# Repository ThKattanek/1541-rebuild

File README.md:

# 1541-rebuild
Ersetzt den Analogteil einer Floppy 1541 durch ein Micro Controller der Disk Images per SD Karte lesen kann. Mit dieser Hardware ist es möglich ein Board wo der Analogteil defekt ist, durch diese wieder zum laufen zu bringen. Das schreiben ist nun auch schon enthalten. Es wird lediglich die 1541 Platine, diese Hardware und ein 5VDC Netzteil benötigt, oder auch das Originale Netzteil. An der 1541 II Platine muss eine Änderungen vorgenommen werden und zwar die (VIA2 (DC) sockeln.

#### ** Danke [F00K42](https://github.com/fook42) für die Entwicklung der Schreibroutinen für D64 Images. **

### [Letzte Offizelle Version findet ihr hier](https://github.com/ThKattanek/1541-rebuild/releases/latest)

### Hardware / Schaltplan
Die Hardware wird mit KiCad entwickelt. Version 5.1.4 unter Ubuntu.

### Hier der Thread dazu im Forum64
https://www.forum64.de/index.php?thread/59884-laufwerk-der-1541-emulieren

### Einige Videos von der 1541-rebuild in aktion
https://youtu.be/EGB8lYKcW-g

https://www.youtube.com/watch?v=MlbUPTzcQGI&t=36s

https://www.youtube.com/watch?v=gKM73VpHdTw&t=256s

### Verwendete Libs
LCD Ansteuerung von Mikrokontroller.net: http://www.mikrocontroller.net/articles/AVR-GCC-Tutorial/LCD-Ansteuerung

SD/FAT System von Roland Riegel: http://www.roland-riegel.de/sd-reader/

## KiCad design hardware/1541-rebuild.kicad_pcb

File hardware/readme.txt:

Die Hardware wurde mit KiCad Version 5.1.4 erstellt.

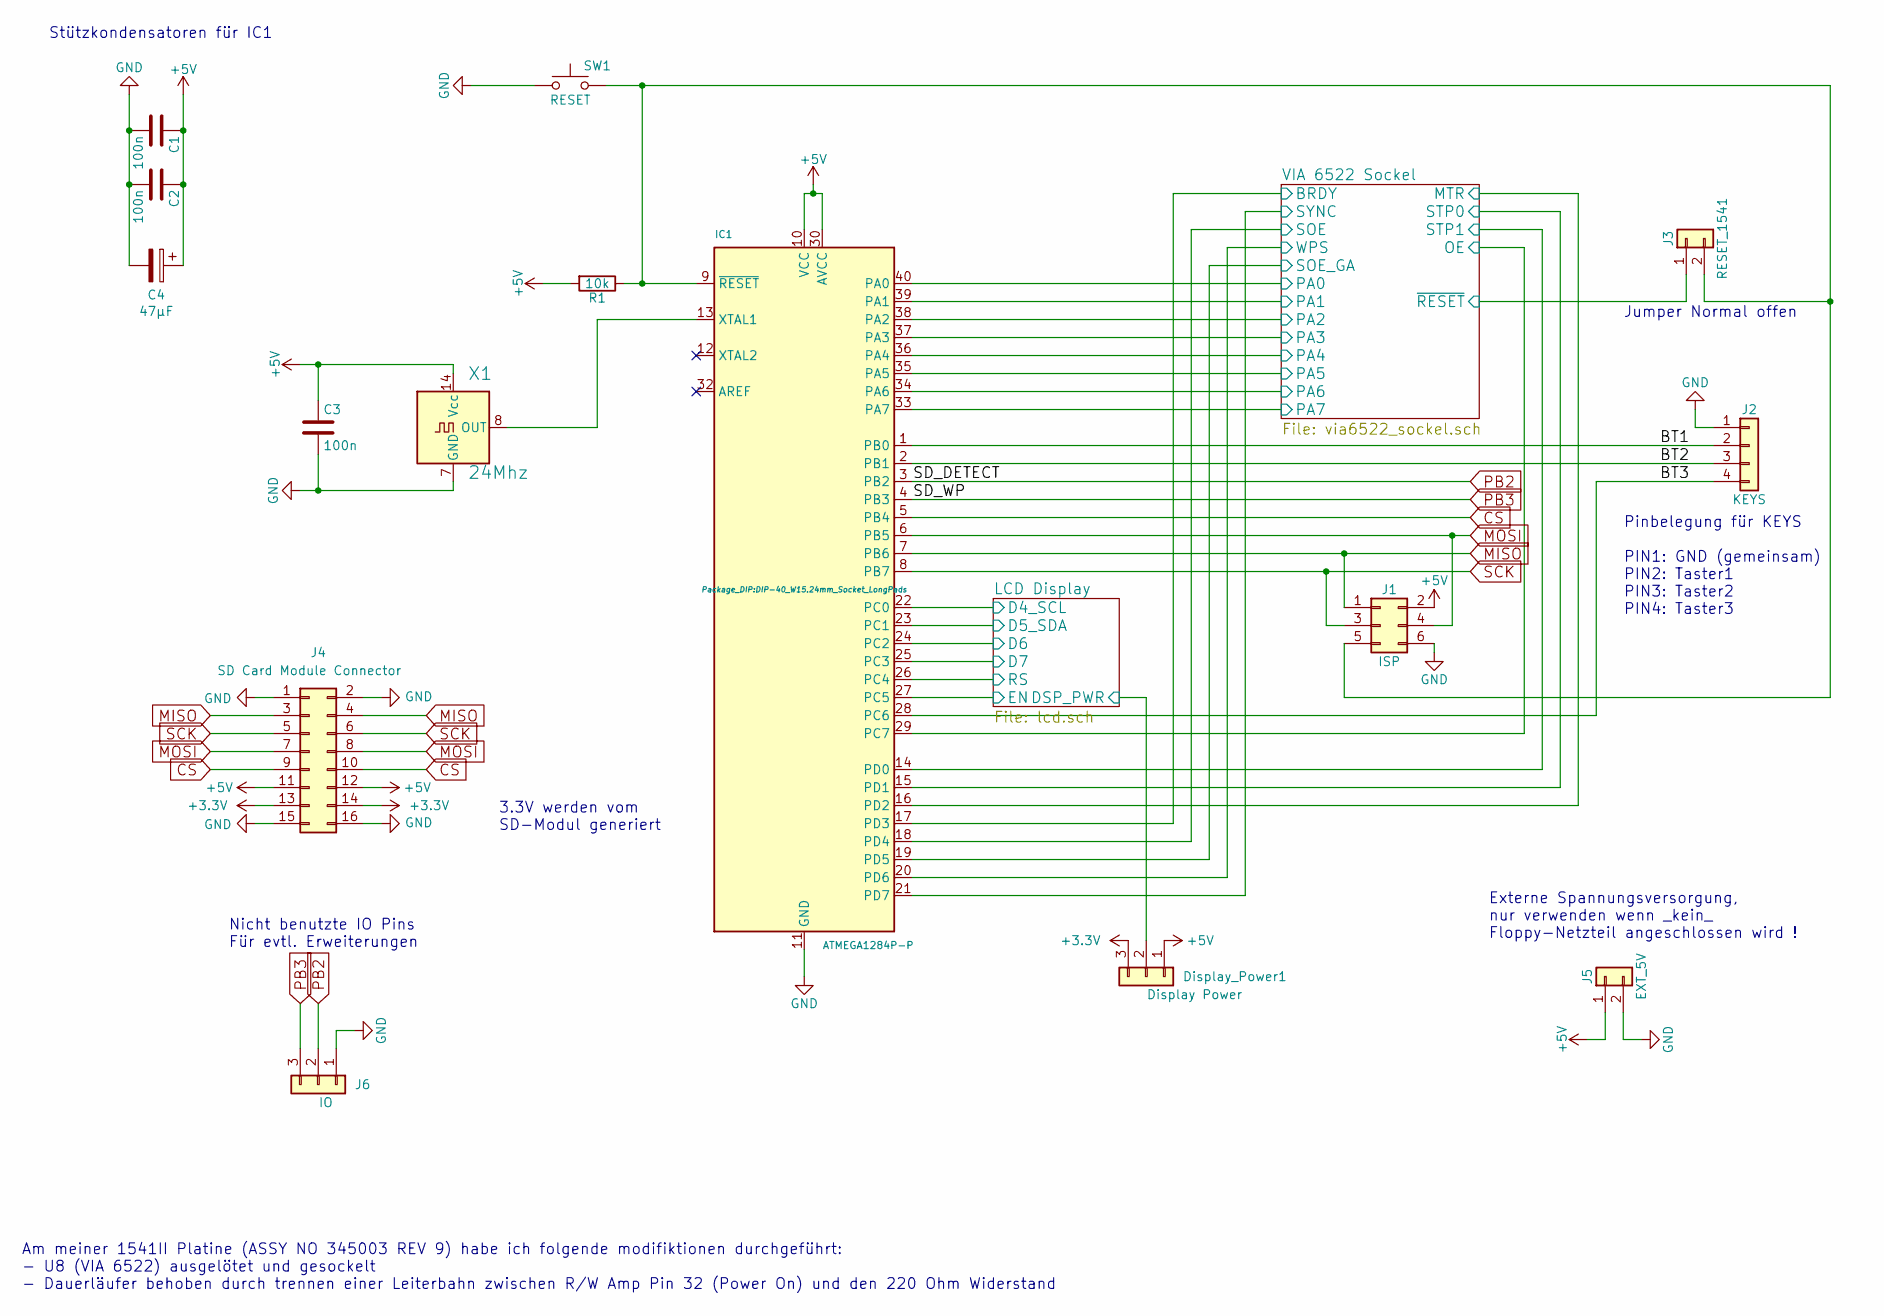
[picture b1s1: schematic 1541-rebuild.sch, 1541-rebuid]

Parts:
C1, C2, C3: 100n; C_Disc_D3.4mm_W2.1mm_P2.50mm
C4: 47µF; CP_Radial_D5.0mm_P2.50mm
Display_Power1: Display Power; PinHeader_1x03_P2.54mm_Vertical
IC1: ATMEGA1284P-P; DIP-40_W15.24mm_Socket_LongPads
J1: ISP; IDC-Header_2x03_P2.54mm_Vertical
J2: KEYS; PinHeader_1x04_P2.54mm_Vertical
J3: RESET_1541; PinHeader_1x02_P2.54mm_Vertical
J4: SD Card Module Connector; PinSocket_2x08_P2.54mm_Vertical
J5: EXT_5V; PinHeader_1x02_P2.54mm_Vertical
J6: IO; PinHeader_1x03_P2.54mm_Vertical
R1: 10k; R_Axial_DIN0207_L6.3mm_D2.5mm_P10.16mm_Horizontal
SW1: RESET; SW_PUSH_6mm_H5mm
X1: 24Mhz; Oscillator_DIP-14_LargePads

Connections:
+3V3: Display_Power1.3, J4.13, J4.14
+5V: C1.1, C2.1, C3.1, C4.1, Display_Power1.1, IC1.10 (VCC), IC1.30 (AVCC), J1.2, J4.11, J4.12, J5.1, R1.2, X1.14 (Vcc); also elsewhere on the board
/BT1: IC1.1 (PB0), J2.2
/BT2: IC1.2 (PB1), J2.3
/BT3: IC1.28 (PC6), J2.4
/LCD Display/D4_SCL: IC1.22 (PC0); also elsewhere on the board
/LCD Display/D5_SDA: IC1.23 (PC1); also elsewhere on the board
/LCD Display/D6: IC1.24 (PC2); also elsewhere on the board
/LCD Display/D7: IC1.25 (PC3); also elsewhere on the board
/LCD Display/DSP_PWR: Display_Power1.2; also elsewhere on the board
/LCD Display/EN: IC1.27 (PC5); also elsewhere on the board
/LCD Display/RS: IC1.26 (PC4); also elsewhere on the board
/VIA 6522 Sockel/BRDY: IC1.17 (PD3); also elsewhere on the board
/VIA 6522 Sockel/MTR: IC1.16 (PD2); also elsewhere on the board
/VIA 6522 Sockel/OE: IC1.29 (PC7); also elsewhere on the board
/VIA 6522 Sockel/PA0: IC1.40 (PA0); also elsewhere on the board
/VIA 6522 Sockel/PA1: IC1.39 (PA1); also elsewhere on the board
/VIA 6522 Sockel/PA2: IC1.38 (PA2); also elsewhere on the board
/VIA 6522 Sockel/PA3: IC1.37 (PA3); also elsewhere on the board
/VIA 6522 Sockel/PA4: IC1.36 (PA4); also elsewhere on the board
/VIA 6522 Sockel/PA5: IC1.35 (PA5); also elsewhere on the board
/VIA 6522 Sockel/PA6: IC1.34 (PA6); also elsewhere on the board
/VIA 6522 Sockel/PA7: IC1.33 (PA7); also elsewhere on the board
/VIA 6522 Sockel/SOE: IC1.18 (PD4); also elsewhere on the board
/VIA 6522 Sockel/SOE_GA: IC1.19 (PD5); also elsewhere on the board
/VIA 6522 Sockel/STP0: IC1.15 (PD1); also elsewhere on the board
/VIA 6522 Sockel/STP1: IC1.14 (PD0); also elsewhere on the board
/VIA 6522 Sockel/SYNC: IC1.21 (PD7); also elsewhere on the board
/VIA 6522 Sockel/WPS: IC1.20 (PD6); also elsewhere on the board
/VIA 6522 Sockel/~RESET: J3.1; also elsewhere on the board
CS: IC1.5 (PB4), J4.9, J4.10
GND: C1.2, C2.2, C3.2, C4.2, IC1.11 (GND), IC1.31 (GND), J1.6, J2.1, J4.1, J4.2, J4.15, J4.16, J5.2, J6.1, SW1.1, X1.7 (GND); also elsewhere on the board
MISO: IC1.7 (PB6), J1.1, J4.3, J4.4
MOSI: IC1.6 (PB5), J1.4, J4.7, J4.8
unnamed: IC1.9 (~RESET), J1.5, J3.2, R1.1, SW1.2
unnamed: IC1.13 (XTAL1), X1.8 (OUT)
PB2: IC1.3 (PB2), J6.2
PB3: IC1.4 (PB3), J6.3
SCK: IC1.8 (PB7), J1.3, J4.5, J4.6

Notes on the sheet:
Am meiner 1541II Platine (ASSY NO 345003 REV 9) habe ich folgende modifiktionen durchgeführt: - U8 (VIA 6522) ausgelötet und gesockelt - Dauerläufer behoben durch trennen einer Leiterbahn zwischen R/W Amp Pin 32 (Power On) und den 220 Ohm Widerstand
Stützkondensatoren für IC1
Jumper Normal offen
Pinbelegung für KEYS PIN1: GND (gemeinsam) PIN2: Taster1 PIN3: Taster2 PIN4: Taster3
Externe Spannungsversorgung, nur verwenden wenn _kein_ Floppy-Netzteil angeschlossen wird !
Nicht benutzte IO Pins Für evtl. Erweiterungen
3.3V werden vom SD-Modul generiert

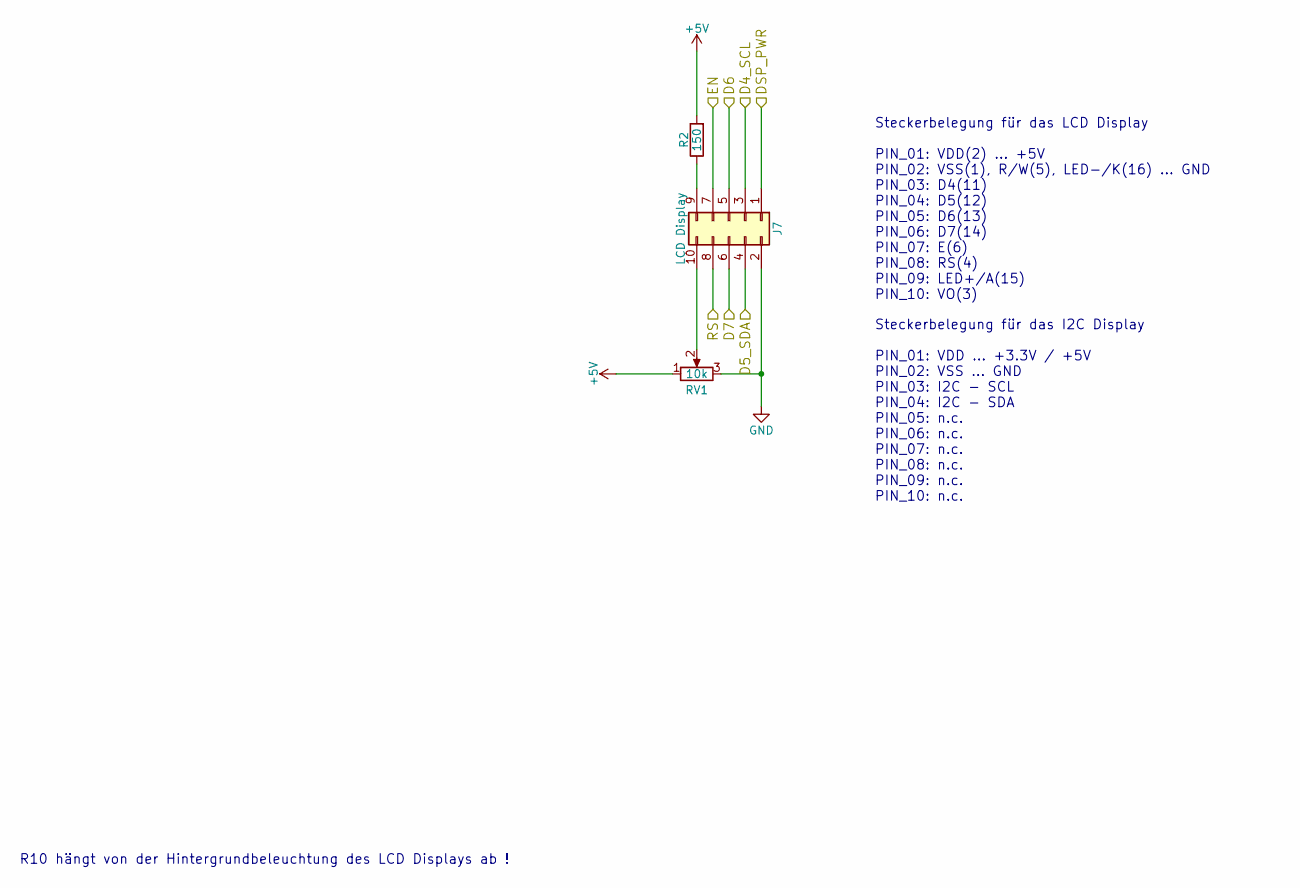
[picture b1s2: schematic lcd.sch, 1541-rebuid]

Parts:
J7: LCD Display; IDC-Header_2x05_P2.54mm_Vertical
R2: 150; R_Axial_DIN0207_L6.3mm_D2.5mm_P10.16mm_Horizontal
RV1: 10k; Potentiometer_Bourns_3296W_Vertical

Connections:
+5V: R2.2, RV1.1; also elsewhere on the board
/LCD Display/D4_SCL: J7.3; also elsewhere on the board
/LCD Display/D5_SDA: J7.4; also elsewhere on the board
/LCD Display/D6: J7.5; also elsewhere on the board
/LCD Display/D7: J7.6; also elsewhere on the board
/LCD Display/DSP_PWR: J7.1; also elsewhere on the board
/LCD Display/EN: J7.7; also elsewhere on the board
/LCD Display/RS: J7.8; also elsewhere on the board
GND: J7.2, RV1.3; also elsewhere on the board
unnamed: J7.9, R2.1
unnamed: J7.10, RV1.2

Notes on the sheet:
Steckerbelegung für das LCD Display PIN_01: VDD(2) ... +5V PIN_02: VSS(1), R/W(5), LED-/K(16) ... GND PIN_03: D4(11) PIN_04: D5(12) PIN_05: D6(13) PIN_06: D7(14) PIN_07: E(6) PIN_08: RS(4) PIN_09: LED+/A(15) PIN_10: VO(3)
R10 hängt von der Hintergrundbeleuchtung des LCD Displays ab !
Steckerbelegung für das I2C Display PIN_01: VDD ... +3.3V / +5V PIN_02: VSS ... GND PIN_03: I2C - SCL PIN_04: I2C - SDA PIN_05: n.c. PIN_06: n.c. PIN_07: n.c. PIN_08: n.c. PIN_09: n.c. PIN_10: n.c.

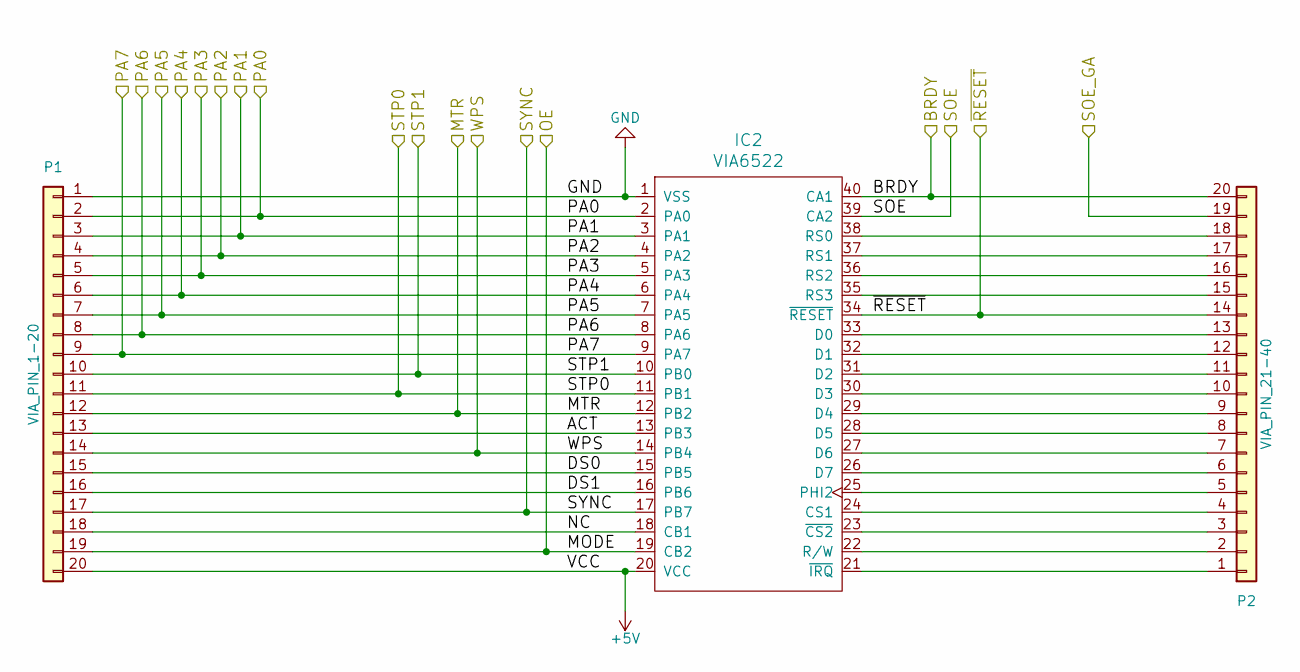
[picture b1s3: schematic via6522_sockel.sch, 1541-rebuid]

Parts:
IC2: VIA6522; DIP-40_W15.24mm_Socket_LongPads
P1: VIA_PIN_1-20; PinHeader_1x20_P2.54mm_Vertical
P2: VIA_PIN_21-40; PinHeader_1x20_P2.54mm_Vertical

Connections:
+5V: IC2.20 (VCC), P1.20; also elsewhere on the board
/VIA 6522 Sockel/ACT: IC2.13 (PB3), P1.13
/VIA 6522 Sockel/BRDY: IC2.40 (CA1), P2.20; also elsewhere on the board
/VIA 6522 Sockel/DS0: IC2.15 (PB5), P1.15
/VIA 6522 Sockel/DS1: IC2.16 (PB6), P1.16
/VIA 6522 Sockel/MTR: IC2.12 (PB2), P1.12; also elsewhere on the board
/VIA 6522 Sockel/NC: IC2.18 (CB1), P1.18
/VIA 6522 Sockel/OE: IC2.19 (CB2), P1.19; also elsewhere on the board
/VIA 6522 Sockel/PA0: IC2.2 (PA0), P1.2; also elsewhere on the board
/VIA 6522 Sockel/PA1: IC2.3 (PA1), P1.3; also elsewhere on the board
/VIA 6522 Sockel/PA2: IC2.4 (PA2), P1.4; also elsewhere on the board
/VIA 6522 Sockel/PA3: IC2.5 (PA3), P1.5; also elsewhere on the board
/VIA 6522 Sockel/PA4: IC2.6 (PA4), P1.6; also elsewhere on the board
/VIA 6522 Sockel/PA5: IC2.7 (PA5), P1.7; also elsewhere on the board
/VIA 6522 Sockel/PA6: IC2.8 (PA6), P1.8; also elsewhere on the board
/VIA 6522 Sockel/PA7: IC2.9 (PA7), P1.9; also elsewhere on the board
/VIA 6522 Sockel/SOE: IC2.39 (CA2); also elsewhere on the board
/VIA 6522 Sockel/SOE_GA: P2.19; also elsewhere on the board
/VIA 6522 Sockel/STP0: IC2.11 (PB1), P1.11; also elsewhere on the board
/VIA 6522 Sockel/STP1: IC2.10 (PB0), P1.10; also elsewhere on the board
/VIA 6522 Sockel/SYNC: IC2.17 (PB7), P1.17; also elsewhere on the board
/VIA 6522 Sockel/WPS: IC2.14 (PB4), P1.14; also elsewhere on the board
/VIA 6522 Sockel/~RESET: IC2.34 (~RESET), P2.14; also elsewhere on the board
GND: IC2.1 (VSS), P1.1; also elsewhere on the board
unnamed: IC2.21 (~IRQ), P2.1
unnamed: IC2.22 (R/W), P2.2
unnamed: IC2.23 (~CS2), P2.3
unnamed: IC2.24 (CS1), P2.4
unnamed: IC2.25 (PHI2), P2.5
unnamed: IC2.26 (D7), P2.6
unnamed: IC2.27 (D6), P2.7
unnamed: IC2.28 (D5), P2.8
unnamed: IC2.29 (D4), P2.9
unnamed: IC2.30 (D3), P2.10
unnamed: IC2.31 (D2), P2.11
unnamed: IC2.32 (D1), P2.12
unnamed: IC2.33 (D0), P2.13
unnamed: IC2.35 (RS3), P2.15
unnamed: IC2.36 (RS2), P2.16
unnamed: IC2.37 (RS1), P2.17
unnamed: IC2.38 (RS0), P2.18

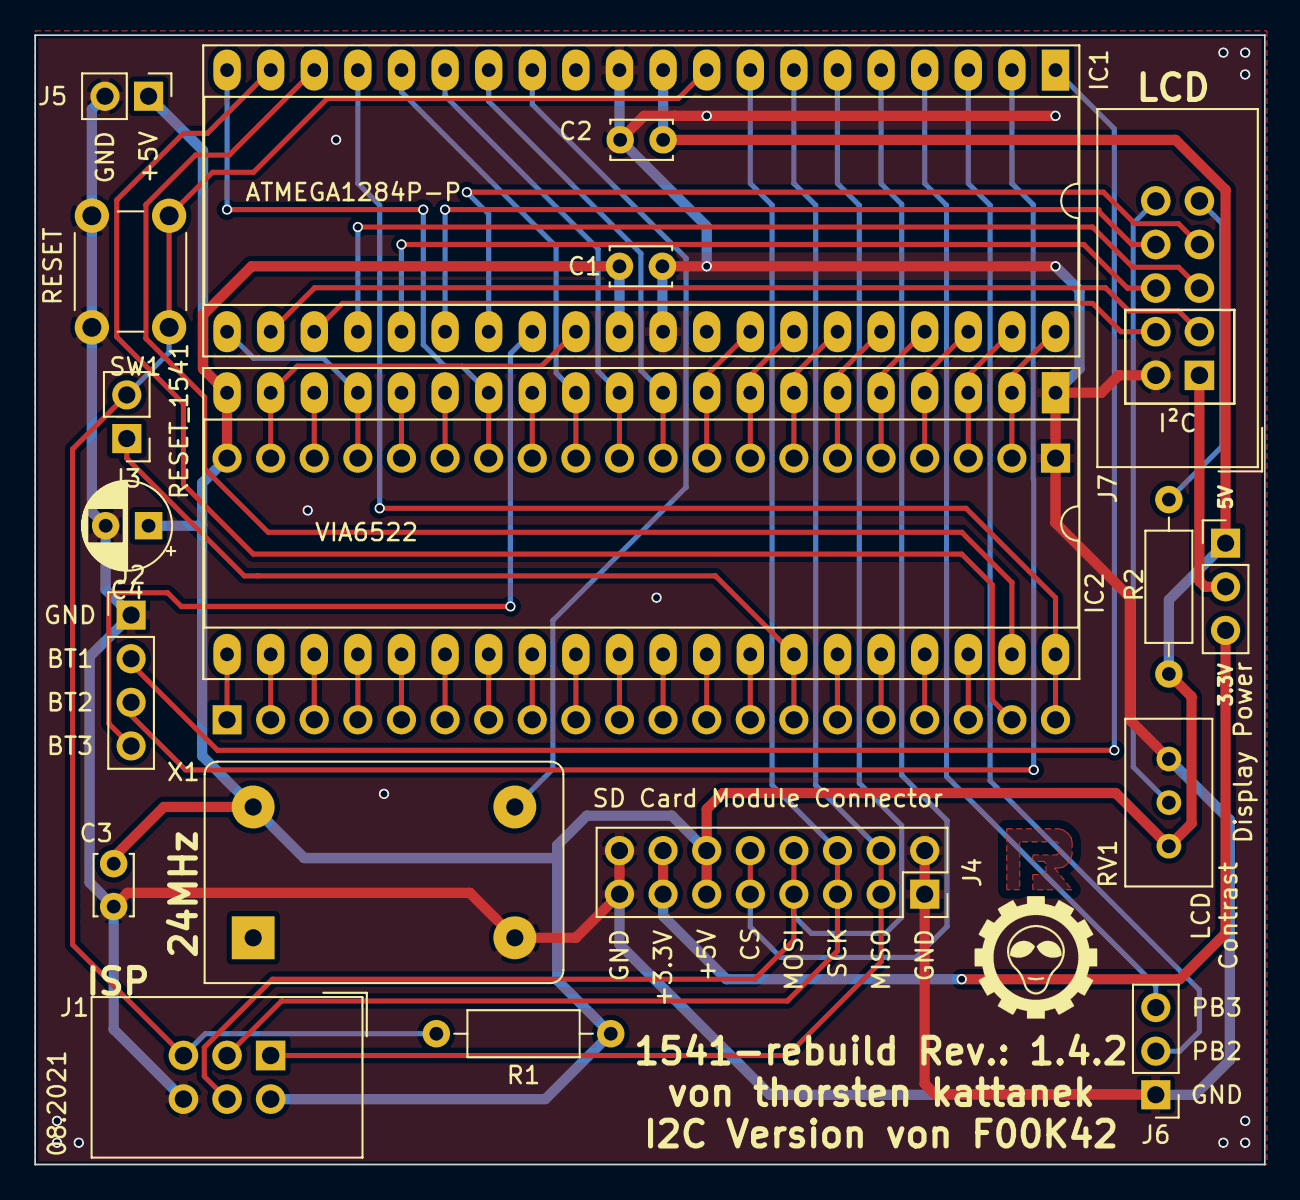
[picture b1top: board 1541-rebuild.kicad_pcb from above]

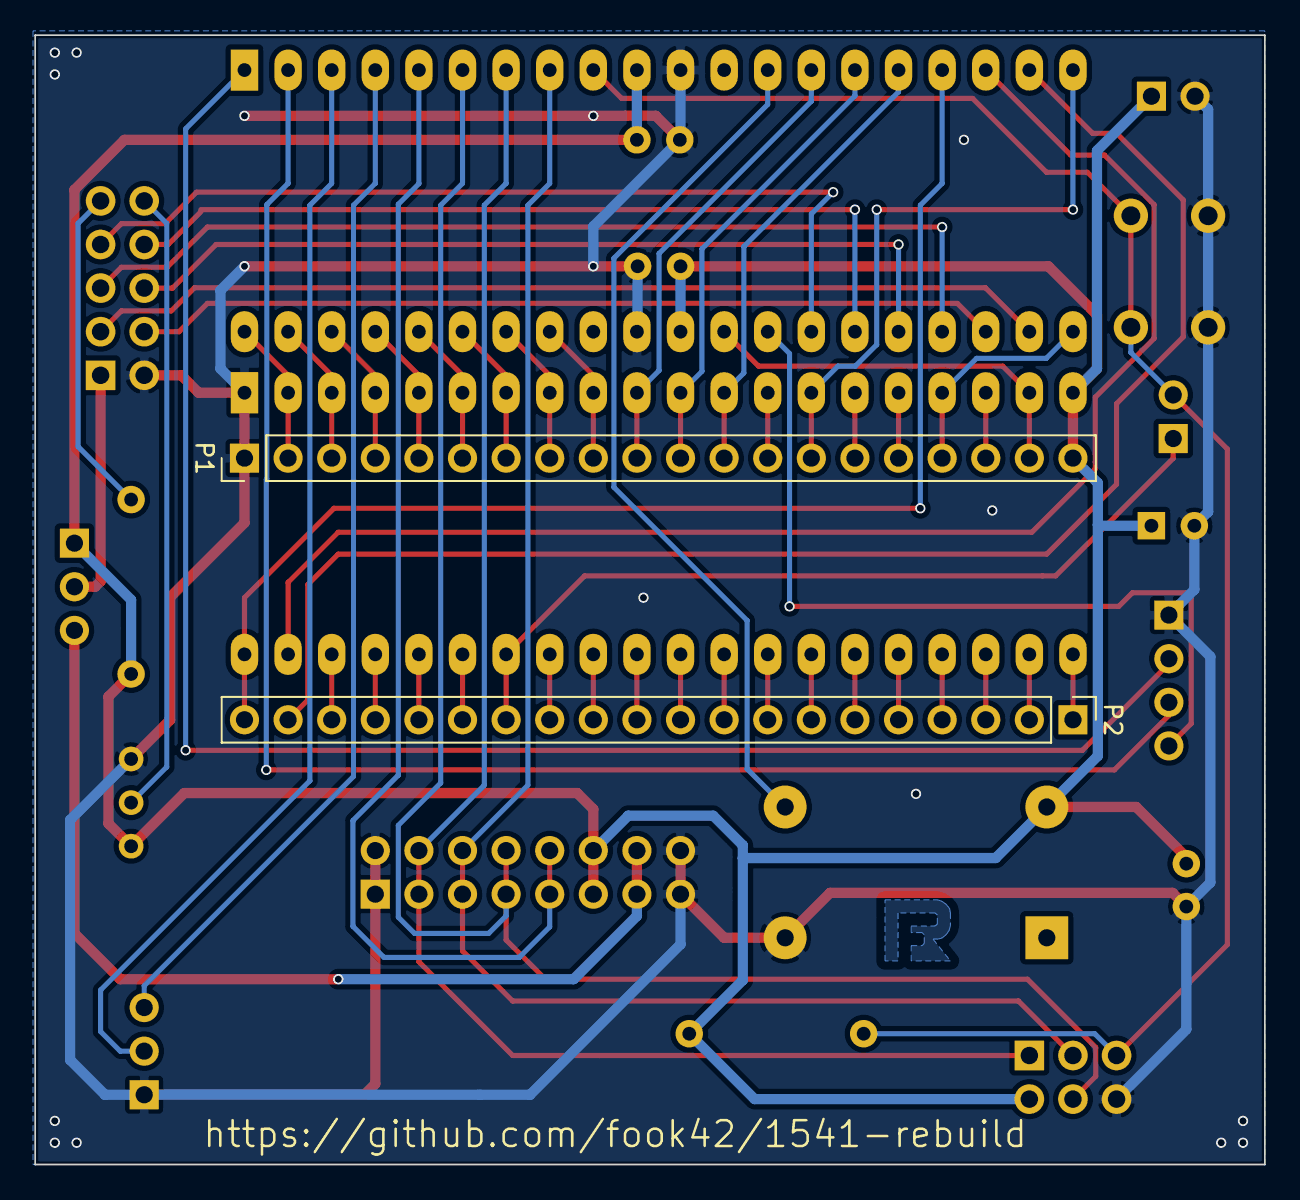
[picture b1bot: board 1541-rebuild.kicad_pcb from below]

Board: 2 copper layers, 71.6 x 65.8 mm, 21 parts (2 on the bottom side), 62 nets.

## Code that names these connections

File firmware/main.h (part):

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// LO wenn SD Karte laufen soll damit ByteReady High bleibt
#define SOE_GATEARRAY_DDR DDRC
#define SOE_GATEARRAY_PORT PORTC
#define SOE_GATEARRAY PC7

// Anschluss der Stepper Signale
// Zwingend diese PINs wegen Extern Interrupts PCINT6/7
// Bei Änderung muss der Sourcecode angepasst werden !
#define STP_DDR  DDRA
#define STP_PIN PINA
#define STP1 PINA6
#define STP0 PINA7

// Anschluss des Laufwerkmotor Signals
#define MTR_DDR DDRC
#define MTR_PIN PINC
#define MTR	PINC2

#define get_motor_status() (MTR_PIN & (1<<MTR))

// Steuersignale
// BYTE READY
#define BYTE_READY_DDR DDRC
#define BYTE_READY_PORT PORTC
#define BYTE_READY  PC0

//DDxn = 0 , PORTxn = 0 --> HiZ
//DDxn = 1 , PORTxn = 0 --> Output Low (Sink)
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
// SYNC
#define SYNC_DDR DDRC
#define SYNC_PORT PORTC
#define SYNC  PC1

#define set_sync() SYNC_PORT |= 1 << SYNC
#define clear_sync() SYNC_PORT &= ~(1 << SYNC)

// SOE
#define SOE_DDR DDRC
#define SOE_PIN PINC
#define SOE	PINC6

#define get_soe_status() (SOE_PIN & (1<<SOE))

// SO
#define SO_DDR DDRC
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// PIN ist mit PIN14 (A) GateArray (Input) verbunden
// PIN ist mit PIN8 LS04 DM74LS04N (Output) verbunden -> Einganag PIN9 hängt auf einen PullUp (47k)
#define WPS_DDR DDRC
#define WPS_PORT PORTC
#define WPS  PC4

#define set_wps() WPS_PORT |= 1 << WPS          // 5V Level = WritePotect
#define clear_wps() WPS_PORT &= ~(1 << WPS)     // 0V Level = Writetable

// Anschluss der Datenleitungen
#define DATA_DDR   DDRD
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inline void ConvertToGCR(uint8_t *source_buffer, uint8_t *destination_buffer);
inline void ConvertFromGCR(uint8_t *source_buffer, uint8_t *destination_buffer);

void endable_wps_port(uint8_t enable);  // 0 = WPS PIN HiZ (set_write_protection() ohne Wirkung) / 1 = WPS PIN als Ausgang
void set_write_protection(int8_t wp);   // wp=0 image nicht geschützt wp=1 image schreibgeschützt
void send_disk_change(void);

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uint8_t akt_image_type = UNDEF_IMAGE;     // 0=kein Image, 1=G64, 2=D64
uint8_t is_image_mount;

uint8_t is_wps_pin_enable = 0; // 0=WPS PIN=HiZ / 1=WPS Output
int8_t floppy_wp = 0;          // Hier wird der aktuelle WriteProtection Zustand gespeichert / 0=Nicht Schreibgeschützt 1=Schreibgeschützt

volatile static uint8_t stp_signals_old = 0;
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
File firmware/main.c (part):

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        /// Image Menü
        MENU_ENTRY image_menu_entrys[] = {{"Insert Image",M_INSERT_IMAGE}, {"Remove Image",M_REMOVE_IMAGE}, {"Write Protect",M_WP_IMAGE,ENTRY_ONOFF,1}, {"New Image",M_NEW_IMAGE}, {"Save Image",M_SAVE_IMAGE}};
        /// Setting Menü
        MENU_ENTRY settings_menu_entrys[] = {{"Pin PB2",M_PIN_PB2, ENTRY_ONOFF, 0}, {"Pin PB3",M_PIN_PB3, ENTRY_ONOFF, 0}, {"Restart",M_RESTART}};
        /// Info Menü
        MENU_ENTRY info_menu_entrys[] = {{"Version",M_VERSION_INFO}, {"SD Card Info",M_SDCARD_INFO}};

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    // Input Mode Setzen
    input_mode = eeprom_read_byte((uint8_t)SETTINGS_INPUT_MODE);

    // WPS PIN Enable
    endable_wps_port(1);

    // Startmeldung ausgeben
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        case M_PIN_PB2:
            if(menu_get_entry_var1(&settings_menu, M_PIN_PB2))
            {
                DDRB |= 1<<PB2;
            }
            else
            {
                DDRB &= ~(1<<PB2);
            }
            menu_refresh();
            break;
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        case M_PIN_PB3:
            if(menu_get_entry_var1(&settings_menu, M_PIN_PB3))
            {
                DDRB |= 1<<PB3;
            }
            else
            {
                DDRB &= ~(1<<PB3);
            }
            menu_refresh();
            break;
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
void init_pb2_pb3()
{
    DDRB &= ~(1<<PB2 | 1<<PB3);
    PORTB |= 1<<PB2 | 1<<PB3;
}

/////////////////////////////////////////////////////////////////////
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
///
/// \brief endable_wps_port
/// \param enable 0 == disable (WPS PIN wird auf Eingang HiZ gestellt)
///               0 != enable  (WPS PIN wird auf Ausgang gestellt, WP wird aktiviert)
///
void endable_wps_port(uint8_t enable)
{
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
ISR (PCINT0_vect)
{
    // Stepper Signale an PA6 und PA7
    stepper_signal_puffer[stepper_signal_w_pos] = STP_PIN & 0xc0;
    stepper_signal_w_pos++;
}
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            if((akt_gcr_byte == 0xff) && (old_gcr_byte == 0xff))        // Prüfen auf SYNC (mindesten 2 aufeinanderfolgende 0xFF)
            {                                                           // Wenn SYNC
                clear_sync();                                           // SYNC Leitung auf Low setzen
                is_sync = 1;                                            // SYNC Merker auf 1
            }
                else
            {                                                           // Wenn kein SYNC
                set_sync();                                             // SYNC Leitung auf High setzen
                is_sync = 0;                                            // SYNC Merker auf 0
            }
        }
        else
        {                                                               // Wenn Motor nicht läuft
            akt_gcr_byte = 0x00;                                        // 0 senden wenn Motor aus
            is_sync = 0;                                                // SYNC Merker auf 0
        }

        // SOE
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
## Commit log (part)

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2015-09-14 Oscilloskopebilder hinzugefügt
2015-09-14 Fotos nach png konvertiert
2015-09-14 Doxyfile angepsst
2015-09-14 KiCad Projekt angefangen
2015-09-14 Fotos vom ersten Testaufbau hinzugefügt
2015-09-14 SD Karten Pinbelegung hinzugefügt
2015-09-14 Info zum SD Karten Anschluss am µC
2015-09-15 Im Schaltplan die SD Karten Anbindung eingefügt
2015-09-15 .bak Dateien aus Repo entfernt.Qscillator im Schaltpan hinzugefügt
2015-09-15 Weiter am Schaltplan gezeichnet ... noch sehr Fehlerhaft
2015-09-16 Schaltplan weiter entwickelt und Layout angefangen
2015-09-16 Aktuellen Schaltplan als PDF exportiert
2015-09-17 Track18 wird nun von SD Karte gelesen und im Speicher abgelegt.
2015-09-20 Sourcecode neu überarbeitet, Schaltplan angepasst und DOC bearbeitet
2015-09-20 Files auf SD Karte durchsehen (root only)
2015-09-20 WPS Signal zum Diskwechsel anzeigen eingebaut. Laden des Track18 eines ausgewählten G64. Schaltpaln aktuallisiert
2015-09-21 Den Sourcecode mal etwas geprdnet.
2015-09-25 Spurwechsel funktioniert jetzt richtig
2015-09-27 Neuer Track wird erst geladen wenn der Stepper mind.20ms still stand.
2015-09-29 Erste funktionierende Version ... Happy git status
2015-09-30 An der Dokumentation weitergeschrieben
2015-10-01 Fotos vom jetzigen Stand hinzugefügt
2015-10-03 Fix: Elvira Arcade und Caren1.1 laufen jetzt auch
2015-10-03 STEPPER_DELAY_TIME auf 15 gestellt
2015-10-04 STEPPER_DELAY_TIME mit 7 ausprobieren.
2015-10-05 Erste Version der neuen Track-Lade Strategie eingebaut
2015-10-05 Beim Image wechsel wird die Aktuelle Spur nicht mit INIT_TRACK neu gesetzt
2016-11-26 Fotos hinzugefügt und KiCad Lib eingefügt
2016-11-26 Neue Fotos verkleinert.
2017-03-28 diverese Sachen geändert
2017-04-02 Platine per Autorouter geroutet.
2018-04-07 PCB Board gelöscht um mit älteren KiCad Versionen kompatibel zu sein.
2018-04-07 readme.md geändert.
2018-04-18 Debug LED im Schaltplan eingefügt.
2018-04-18 Debug LED Ansteuerung in der Firmaware eingefügt.
2018-04-18 BugFix: Stepperänderung wurde nicht mehr erkannt. Und somit kein laden mehr möglich gewesen. Problem war eine zu frühe Zeiger erhöhung.
2018-04-21 Änderungen am Schaltplan: - Resettaster eingefügt - SD Card Slot -> WP und DETECT richtig angeschlossen - auf Version 1.2 hochgesetzt
2018-04-22 G64 Support -> Bugfix -> G64 lesen geht nun Schreiben auf G64 funktioniert auch. D64 noch nicht! BugFix -> ComaLight 13 absturtz nach wechsel auf Seite 2 -> läuft jetzt
2018-04-22 - Nochmal kleine Anpassung (no_send_ready wieder raus dafür timer stop/ start) - Version 1.2.0
2018-04-22 Komando zurück --> no_send_ready bleibt vorrerst drin ! Sonst gibt es probleme beim schreiben (StopTimer0 reicht nicht)
2018-04-23 Angefangen alle Warnmeldungen des gcc-avr compilers zu bearbeiten.
2018-04-23 Weitere Warnmeldungen beseitigt.
2018-04-23 Write Protection kann jetzt per Function set_write_protection aktiviert oder deaktiviert werden. Brücke für CONN4 ist nicht mehr nötig für Diskwechsel. Bitraten für die 4 Time-Zonen etwas verlangsamt.
2018-04-23 Diskwechsel wird durch wechseln des wps Signals gekennzeichnet. Ich habe die Zeit auf 3ms gesetzt.
2018-04-25 TimeZone wieder auf Original gesetzt Heade GAP Byte auf 9 gesetzt -> bei der Umwandlung d64-gcr
2018-04-25 - kein stop_timer0 mehr, beim laden des Tracks - WritePotection wird bei D64 immer gesetzt und bei G64 immer nicht gesetzt
2018-05-04 Umgestellt auf 24MHz
2018-05-04 Schaltplan angepasst und Takt auf 24MHz geändert. Revision auf 1.2.1 gesetzt.
2018-05-05 .gitignore angepasst
2018-05-05 - auf Version 1.2.2 gesetzt - diverse optimierungen am Trackwechsel - Diskchange überarbeitet
2018-05-05 LCD Display wird nun als 10 PIN Wannenstecker rausgeführt. PIN Belegung des Steckers wird im Schaltplan beschrieben.
2018-05-05 Im Schaltplan die 3 Steuertasten als 4 PINS (Key1, Key2, Key3 und GND) rausgeführt. Auf Revesion 1.3.2 gesetzt.
2018-05-06 Test Commit
2018-05-06 Allen Bauteilen Footprints zugeordnet.
2018-05-06 - Anordnung aller Bauteile (Problem noch mit SD-Slot) - Erstes PCB Layout mit Freeroute - Autorouter.
2018-05-08 BOM als csv in der doc hinzugefügt
2018-05-08 - Hardware nochmal angepasst - erstes Layout erstellt - Schaltplan auf Rev.1.3.4 gesetzt
2018-05-11 Borad fertig gestellt und auf rev 1.3.5 gesetzt Gerberfiles erzeugt und als rar gepackt. Mit PCB Hersteller -Seedstudio- getestet.
2018-05-11 3d ansicht der Hardware geändert --- 3D View von KiCad
2018-07-23 1541-rebuild.png angepasst. --> real Foto
2020-03-22 added iec_captures
2020-04-14 Hardwareverzeichnis gesäubert
2020-04-14 - 1541-rebuild Platinen Foto von /hardware nach doc/fotos - README.md angepasst
2020-04-17 Platine geändert - größe angepasst für 1541 I + II - Bauteile neu angeordnet - Beschriftungen hinzugefügt
2020-04-17 Platine geändert - größe nochmals angepasst an 1541 II, 1541 kurz, 5141 mittel - Bauteile neu angeordnet
2020-04-18 readme.md geändert - Text überarbeitet - neues Bild eingefügt
2020-04-18 Platine geändert - link zum GitHub Repository als Beschriftung hinzugefügt
2020-04-18 firmware angepasst an neues pcb layout - SOE am GateArray kann nun vom AtMega getseuert werden, für 1541-rebuild muss das auf lo gesetzt werden - damit ist ByteReady dauerhaft auf Hi und kann auch so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
2020-04-18 Schaltplan als PDF in doc exportiert
2020-04-30 Stückliste neu erstellt
2020-04-30 bom angepasst
2020-04-30 fotos vom Board rev 1.4.0 hinzugefügt
2020-04-30 2 Fotos in die Dokumentation eingefügt
2020-05-01 doc geändert
2020-05-01 Dokumentation überarbeitet - Aufbauanleitung hinzugefügt - Menü erweitert
2020-05-03 PIN's für SD Card Detect und WritePotection deaktiviert - die SD Karte ist somit immer beschreibbar und vorhanden für die SDLib
2020-05-03 Debug Ausgaben entfernt.
2020-05-03 WPS PIN als Standard erstmal auf Hi-Z - somit ist der Schreibschutz momentan nur über den PIN3 des CN4 steuerbar - offen Disk ist immer WritePotect - auf GND Disk kann beschrieben werden
2020-05-07 bedienung_entwurf.txt zu doc hinzugefügt
2020-05-07 bedienung_entwurf.txt geändert
2020-05-07 add menu.h
2020-05-08 code weiter in kleinere module aufgeteilt
2020-05-08 gcr_track18.h entfernt
2020-05-08 firmware: - tasten auswertung nun via timer0 isr und tastaturpuffer (16 byte groß) - get_key_from_buffer hinzugefuegt
2020-05-09 Makefile -> utf-8
2020-05-13 Start LCD MENU Simulation für PC (Qt)
2020-05-16 Firmware: - Startmessage hinzugefuegt
2020-05-17 Firmware: - added menu.c
2020-05-20 changed doc/bedienung_entwurf.txt
2020-05-20 Firmware - delete include iostream in menu.h
2020-05-21 Firmware: - menu_update in update_gui eingehaeng - gui konstanten in gui_constants.h ausgelagert
2020-05-21 Firmware: - Erste Menüstruktur Auswertung und erste Anzeige - MenuSimulation angepasst.
2020-05-21 Firmware: - menu wird angezeigt und ist scrollbar
2020-05-22 Firmware: - Menusystem erst einmal fertig gestellt
2020-05-22 Firmware: - Remove Image hinzugefügt - Write Protect eingebaut - Menu Framework um weitere Menu Entry Typen erweitert - ON/OFF, BOOL, BIN
2020-05-22 Firmware: - Settings Menü hinzugefügt mit Debug LED
2020-05-22 Firmware: - benutzerdifinierte Pfeil für Menü Cursor (Code 2 statt 126)
2020-05-22 Firmware: - fixed menu_refresh
2020-05-22 Firmware: - Anpassung für Menu_Sim
2020-05-23 Firmware: - Menu Framework verbessert
2020-05-23 Firmware: - Restart unter Settings eingebaut - Info ist jetzt ein Untermenue und kann jetzt die Version anzeigen oder infos zur eingelgten SD Karte
2020-05-23 Dokumentation: - Aufbauanleitung Fehler beseitigt: (Oszillator falsche Einbaurichtung beschrieben) - Angefangen die kommende FW 1.3.0 zu Dokumentieren
2020-05-23 Firmware: - filebrowser_update & filebrowser_refresh angelegt
2020-05-23 Firmware: - seek_to_dir_entry korrigiert --> funktioniert nun
2020-05-24 Firmware: - neue KEY Events hinzugefuegt KEY2_TIMEOUT1, KEY2_TIMEOUT2 - werden aufgerufen bei längeren drücken des KEY2
2020-05-24 Firmware: - Laengeres druecken der Entertaste bedeutet immer zuruck oder abbruch - Menuepunke "Back" aus allen Menus entfernt
2020-05-24 Firmware: - lcd_print zur LCD Lib hinzugefuegt
2020-05-24 Firmware: - kleinen Fehler in lcd_print beseitigt
2020-05-26 Schaltplan 1541 pcd #250448
2020-05-26 Dokumentation: - SD Karten und Filesystem hinzugefügt
2020-05-30 Firmware: - Drehencoder wird nun unterstützt
2020-05-30 Firmware: - Umschaltumg zwischen Drehencoder & Buttons vorbereitet
2020-06-01 Firmware: - Settings werden nun ins EEPROM geschrieben
2020-06-01 Firmware: - Umschaltung zwischen Button Mode und Encoder Mode eingebaut - Ins Settings Menue Pin PB2 und Pin PB3 aufgenommen - Debug LED wieder rausgenommen
2020-06-01 Dokumentation: - Dokumentation weiter angepasst
2020-06-01 Dokumentation: - Beschreibung Anschluss LCD Display eingefuegt
2020-06-03 Dokumentation: - Flashen aktuallisiert
2020-06-03 Auf Version 1.3.0 gesetzt
2020-09-03 Firmware: Makefile geändert, um Binary Files gleich mit zu erzeugen
2021-01-24 .gitignore geändert
2021-08-21 added i2c-files to Makefile and main.h
2021-08-21 main.c changed from CR+LF to LF
2021-08-22 implemented LCD 1602 support + minor code improvements
    optimized lcd setcursor routine, included LCD size-defines for
    easier adoption to different LCD sizes. adjusted all lcd-text positions,
    reduced text-length where possible to <= 16 chars.
    found small improvment for track-read, corrected some compiler warnings.
    cleaned up code for better readability (clean C etc)
2021-08-22 minor corrections to display-strings
2021-08-23 major changes for 1.4.1 PCB
    created a new PCB for I2C support. all connections rerouted and
    a new board needs to be created. layout and footprint taken from 1.4.0
    board revision. images from kicad added, README adopted
    CAUTION: PCB untested, due to lack of software routines (I2C)
2021-08-24 Update README.md
    more information on new 1.4.1 PCB and current status
2021-08-25 modified 1.4.1 PCB
    added capacitor for better power-supply stability
    minor changes for silkscreen texts and groundplane
2021-08-27 copied pcb-changes from master-branch
2021-08-27 added PCB 1.4.2 gerbers
2021-08-28 i2c-routines for LCD display communication
    implemented adopted i2c-routines for PCF8574 portexpander
    lcd is connected to PCF8574 -> new lcd-routines developed
    firmware version number change to 1.3.2 corresponds with pcb 1.4.2
2021-08-28 updated README, schematics PDF and included Images
2021-09-12 updated documentation, README.md, images, BOM, PDFs
2021-09-17 added detection of I2C-device between 0x20-0x27 and 0x38-0x3F
2021-09-17 I2C autodetect .. more cleanup
2021-09-18 I2C freq back to 100kHz, cleanup
2021-09-18 implemented display autodetection, preparation for OLED
    reworked complete display-handling - detection of I2C/10pin Displays
    LCD display routines converted to handle both types automatically
    prepared OLED display handling - detection of OLED-I2C Address is done
    bumped software-version to 1.3.4
2021-09-19 first OLED implementation done - SW 1.3.5
2021-09-19 OLED: corrected Font, special chars included
2021-09-19 updated README.md with OLED image
2021-09-29 Update README.md
    manually merged original README with new 1.4.2/1.3.5 data
2021-11-30 minor fix for Font-definition ... not visible
2021-12-04 D64 write support implemented
    routines taken from fook42/1541-rebuild fork.
    GCR decoding according to lft description - improved
    pointer handling and combined lookup table for better
    performance.
    known issues: writing of multiple tracks leads to data corruption
2021-12-18 updated GCRroutines, D64write transfer from fork
2021-12-18 rm main.lst and main.o from repo
2021-12-20 D64: extraction of Floppy-IDs from Track18-Area
    reads 2 bytes from Track18 - Offset $A2+$A3 and stores it in
    global variables for GCR track creation.
    fixes issue #33
2021-12-20 D64: extraction of FloppyID .. fixed typecast to int32_t

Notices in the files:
firmware/main.c:
Copyright: (c) 2020 by Thorsten Kattanek <thorsten.kattanek@gmx.de>
License: GPL 2
